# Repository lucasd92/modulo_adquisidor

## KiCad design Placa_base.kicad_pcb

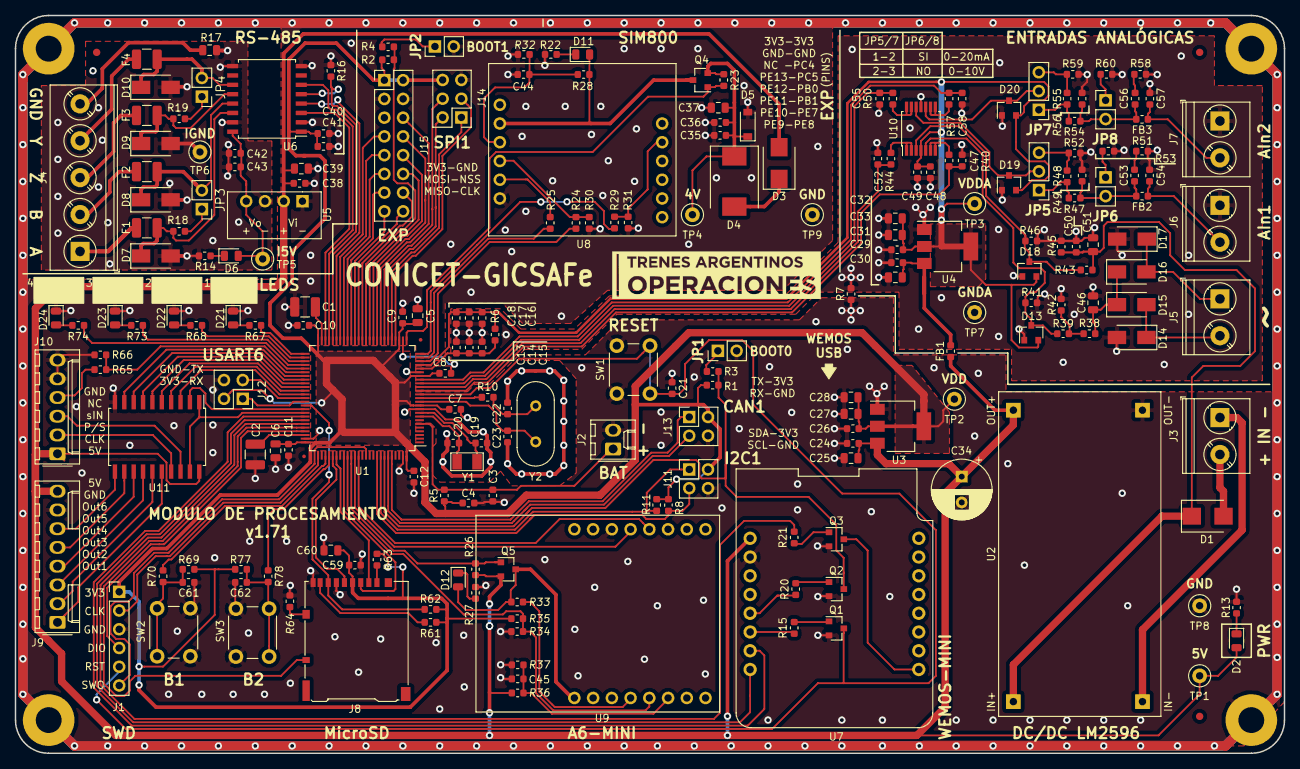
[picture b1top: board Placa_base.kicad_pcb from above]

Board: 2 copper layers, 172.0 x 100.0 mm, 228 parts (0 on the bottom side), 162 nets.

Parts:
C1, C2: 2.2uF; C_1210_3225Metric
C3, C15, C17, C40, C42, C48: 1Uf; C_0603_1608Metric
C4, C7, C8, C9, C10, C11, C12, C14, C16, C21, C24, C26, C29, C31, C38, C41, C43, C44, C45, C47, C49, C50, C52, C55, C58, C59, C61, C62: 100nF; C_0603_1608Metric
C5, C6: 4.7uF; C_0805_2012Metric
C13, C18: 10nF; C_0603_1608Metric
C19, C20: 1.5pF; C_0603_1608Metric
C22, C23: 20pF; C_0603_1608Metric
C25, C27, C28, C30, C32, C33, C37, C39, C46, C51, C60: 10uF; C_0805_2012Metric
C34: 820uF 10V; CP_Radial_D8.0mm_P3.50mm
C35: 10p; C_0603_1608Metric
C36: 33p; C_0603_1608Metric
C53, C56: 470pF; C_0603_1608Metric
C54, C57: 1nF; C_0603_1608Metric
D1, D3: S5JB-R5G; D_SMB
D2, D6, D11, D12, D21, D22, D23, D24: LED; LED_0805_2012Metric
D4: B340; D_SMC
D5: BZT52-B5V1X; D_SOD-123
D7, D8, D9, D10: SMAJ12CA-TR; D_SMA
D13, D18, D19, D20: BAV99; SOT-23
D14, D15, D16, D17: MRA4007T3G; D_SMA
F1, F2, F3, F4: USMF020; R_1210_3225Metric
FB1: Ferrite_Bead; R_0603_1608Metric
FB2, FB3: MMZ1608B601C; R_0603_1608Metric
FD1, FD2, FD3: Fiducial; Fiducial_1mm_Dia_2mm_Outer
FD4, FD5: Fiducial; Fiducial_0.5mm_Dia_1mm_Outer
G1: TrenesArgentinosLogo; TrenesArgentinosLogoNeg
H1, H2, H3, H4: MountingHole_Pad; MountingHole_3.5mm_Pad
J1: SWD/STLINK; PinHeader_1x06_P2.54mm_Vertical
J2: Bateria; Molex_KK-254_AE-6410-02A_1x02_P2.54mm_Vertical
J3: Entrada 24V; TerminalBlock_Phoenix_PT-1,5-2-5.0-H_1x02_P5.00mm_Horizonta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
J4: RS-485; TerminalBlock_Phoenix_PT-1,5-5-5.0-H_1x05_P5.00mm_Horizonta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
J5: TV_6V; TerminalBlock_Phoenix_PT-1,5-2-5.0-H_1x02_P5.00mm_Horizonta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
J6: AN1; TerminalBlock_Phoenix_PT-1,5-2-5.0-H_1x02_P5.00mm_Horizonta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
J7: AN2; TerminalBlock_Phoenix_PT-1,5-2-5.0-H_1x02_P5.00mm_Horizonta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
J8: Micro_SD_Card_Det_Hirose_DM3AT; microSD_HC_Hirose_DM3AT-SF-PEJM5
J9: Salidas 5V; Molex_KK-254_AE-6410-08A_1x08_P2.54mm_Vertical
J10: Interfaz con entradas digitales (CD4021); Molex_KK-254_AE-6410-06A_1x06_P2.54mm_Vertical
J11: I2C1; PinHeader_2x02_P2.54mm_Vertical
J12: USART6; PinHeader_2x02_P2.54mm_Vertical
J13: CAN1; PinHeader_2x02_P2.54mm_Vertical
J14: SPI1; PinHeader_2x03_P2.54mm_Vertical
J15: EXP; PinHeader_2x08_P2.54mm_Vertical
JP1, JP2: Jumper_2_Open; PinHeader_1x02_P2.54mm_Vertical
JP3, JP4: Jumper; PinHeader_1x02_P2.54mm_Vertical
JP5, JP7: 1/3-2/3; PinHeader_1x03_P2.54mm_Vertical
JP6, JP8: I_meas; PinHeader_1x02_P2.54mm_Vertical
Q1, Q2, Q3: MMBT3904; SOT-23
Q4, Q5: AO3401; SOT-23
R1, R2: 10K; R_0603_1608Metric
R3, R4: 510; R_0603_1608Metric
R5, R7, R28, R32, R33, R34, R35, R36, R37, R42, R45, R49, R56, R64: 0; R_0603_1608Metric
R6: 47; R_0603_1608Metric
R8, R11: 4K7; R_0603_1608Metric
R10: CALCULAR; R_0603_1608Metric
R13, R14, R22, R27, R70, R78: 1k; R_0603_1608Metric
R15, R20, R21, R24, R25, R29: 1K; R_0603_1608Metric
R16, R30, R31: 5K6; R_0603_1608Metric
R17: 100 1/2W; R_0805_2012Metric
R18, R19: 120; R_0603_1608Metric
R23, R26: 150k; R_0603_1608Metric
R38, R39, R41, R47, R48, R52, R54, R55, R59: 15k; R_0603_1608Metric
R40, R44, R50, R57: 1.5k; R_0603_1608Metric
R43: 47k; R_0603_1608Metric
R46: 12k; R_0603_1608Metric
R51, R58: 4.7; R_0603_1608Metric
R53, R60, R65: 220; R_0603_1608Metric
R61, R62, R63: 56K; R_0603_1608Metric
R66: 330; R_0603_1608Metric
R67, R68, R73, R74: 260; R_0603_1608Metric
R69, R77: 10k; R_0603_1608Metric
SW1, SW2, SW3: SW_Push; SW_PUSH_6mm_H9.5mm
TP1, TP2, TP3, TP4, TP5, TP6, TP7, TP8, TP9: TestPoint; TestPoint_Loop_D2.50mm_Drill1.0mm
U1: STM32F407VGTx; LQFP-100
U2: DC-DC_Step-Down; modulo_dc-dc-LM2596
U3, U4: AZ1117-3.3; SOT-223-3_TabPin2
U5: RFM-0505S; SIP4-RFM0505S
U6: ISO1412; SOIC-16W_7.5x10.3mm_P1.27mm
U7: WeMos_mini; wemos-d1-mini-with-pin-header-and-connector
U8: SIM800L_modulo; SIM800L_mod
U9: Modulo_A6_Mini; Modulo_A6_mini
U10: MCP6L04T-E/ST; TSSOP-14_4.4x5mm_P0.65mm
U11: 74HCT541; SOIC-20W_7.5x12.8mm_P1.27mm
Y1: 32.768KHz; Cristal 32KHz
Y2: 8MHz; Crystal_HC49-4H_Vertical

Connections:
+4V: C35.1, C36.1, C37.1, D4.1, D5.1, Q4.2, R23.2, TP4.1
+5P: C42.1, C43.1, D6.2, TP5.1, U5.4, U6.16
+5V: C24.1, C25.1, C34.1, C38.1, C39.1, D2.2, D3.2, FB1.1, J9.8, J10.1, Q5.2, R26.1, R36.2, TP1.1, U2.3, U3.3, U5.2, U7.1, U11.20
/A6_INT: R34.1, R35.2, U1.84, U9.5
/A6_ON: Q5.1, R26.2, U1.85
/An_In1: C47.1, R40.2, U1.15
/An_In2: C52.1, R44.2, U1.16
/An_In3: C55.1, R50.2, U1.17
/An_In4: C58.1, R57.2, U1.18
/BOOT0: Q2.3, R1.2, R3.1, U1.94
/CAN1_RX: J13.3, U1.95
/CAN1_TX: J13.1, U1.96
/DIO/in_clk: J10.2, U11.17
/DIO/par_ser: J10.3, U11.18
/EXP_PIN1: J15.6, U1.33
/EXP_PIN2: J15.7, U1.44
/EXP_PIN3: J15.8, U1.34
/EXP_PIN4: J15.9, U1.43
/EXP_PIN5: J15.10, U1.35
/EXP_PIN6: J15.11, U1.42
/EXP_PIN7: J15.12, U1.36
/EXP_PIN8: J15.13, U1.41
/EXP_PIN9: J15.14, U1.38
/EXP_PIN10: J15.15, U1.40
/EXP_PIN11: J15.16, U1.39
/I2C1_SCL: J11.3, R8.1, U1.92
/I2C1_SDA: J11.1, R11.1, U1.93
/IN_CLK: U1.62, U11.3
/IN_P-S: U1.66, U11.2
/IN_Read: R65.1, R66.2, U1.55
/LED1: R67.1, U1.51
/LED2: R68.1, U1.52
/LED3: R73.1, U1.53
/LED4: R74.1, U1.54
/MCU/PB2-BOOT1: R2.2, R4.1, U1.37
/MCU/PC14: C20.1, U1.8, Y1.2
/MCU/PC15: C19.1, U1.9, Y1.1
/MCU/PH0: C23.1, U1.12, Y2.2
/MCU/PH1: R10.1, U1.13
/MCU/TCK-SWCLK: J1.2, U1.76
/MCU/TDO-SWO: J1.6, U1.89
/MCU/TMS-SWDIO: J1.4, U1.72
/MCU/VBAT: C3.1, J2.1, R5.2, U1.6
/MCU/VREF+: C13.1, C14.1, C15.1, R6.2, U1.21
/NRST: C21.1, J1.5, Q1.3, SW1.1, U1.14
/OUT_1: U1.61, U11.4
/OUT_2: U1.60, U11.5
/OUT_3: U1.59, U11.6
/OUT_4: U1.58, U11.7
/OUT_5: U1.57, U11.8
/OUT_6: U1.56, U11.9
/OUT_EN: U1.67, U11.1, U11.19
/RS-485_D: U1.47, U6.6
/RS-485_DE: R16.2, U1.46, U6.5
/RS-485_R: U1.48, U6.3
/RS-485_RE: U1.45, U6.4
/Reset_ESP: R21.1, U1.70
/S800_DTR: R29.1, U1.25
/S800_ON: Q4.1, R23.1, U1.26
/SPI1_CK: J14.1, U1.30
/SPI1_MISO: J14.2, U1.31
/SPI1_MOSI: J14.4, U1.32
/SPI1_NSS: J14.3, U1.29
/SW1: R70.2, U1.78
/SW2: R78.2, U1.79
/USART1_RX: U1.69, U7.8
/USART1_TX: U1.68, U7.7
/USART2_RX: U1.87, U9.12
/USART2_TX: U1.86, U9.13
/USART4_RX: R25.1, U1.24
/USART4_TX: R24.1, U1.23
/USART6_RX: J12.1, U1.64
/USART6_TX: J12.3, U1.63
/WiFi/A: D7.1, F1.2, R18.2, U6.14
/WiFi/B: D8.1, F2.2, JP3.2, U6.13
/WiFi/DTR_SIM800: R29.2, R31.2, U8.11
/WiFi/RX_SIM800: R24.2, R30.2, U8.4
/WiFi/TX_SIM800: R25.2, U8.5
/WiFi/Y: D10.1, F4.2, JP4.2, U6.11
/WiFi/Z: D9.1, F3.2, R19.2, U6.12
/analogico/AIn1: C50.1, C51.1, D1.1, R43.1, R45.1, U2.1
/uSD_CD: J8.2, U1.81
/uSD_CK: J8.5, U1.80
/uSD_Cmd: J8.3, U1.83
/uSD_D0: J8.7, R62.1, U1.65
/uSD_Det: J8.10, U1.71
Earth: C42.2, C43.2, D7.2, D8.2, D9.2, D10.2, R14.1, R17.1, TP6.1, U5.3, U6.9, U6.15
GND: C1.2, C2.2, C3.2, C4.2, C5.2, C6.2, C7.2, C8.2, C9.2, C10.2, C11.2, C12.2, C19.2, C20.2, C21.2, C22.2, C23.2, C24.2, C25.2, C26.2, C27.2, C28.2, C34.2, C35.2, C36.2, C37.2, C38.2, C39.2, C40.2, C41.2, C44.2, C45.2, C59.2, C60.2, C61.2, C62.2, D5.2, D21.1, D22.1, D23.1, D24.1, H1.1, H2.1, H3.1, H4.1, J1.3, J2.2, J8.6, J8.9, J9.7, J10.5, J10.6, J11.4, J12.4, J13.4, J14.5, J15.3, J15.4, JP1.2, JP2.2, Q1.2, Q2.2, Q3.2, R7.1, R13.2, R16.1, R22.1, R27.1, R30.1, R31.1, R32.1, R35.1, R37.1, R64.1, R66.1, SW1.2, SW2.2, SW3.2, TP8.1, TP9.1, U1.10, U1.27, U1.74, U1.99, U2.4, U3.1, U5.1, U6.2, U6.8, U7.2, U8.6, U9.14, U11.10
GNDA: C13.2, C14.2, C15.2, C16.2, C17.2, C18.2, C29.2, C30.2, C31.2, C32.2, C33.2, C46.2, C47.2, C48.2, C49.2, C50.2, C51.2, C52.2, C54.2, C55.2, C57.2, C58.2, D13.1, D14.2, D16.2, D18.1, D19.1, D20.1, J6.1, J7.1, R7.2, R41.2, R42.2, R45.2, R46.2, R49.2, R51.1, R52.2, R53.1, R56.2, R58.1, R59.2, R60.1, TP7.1, U1.20, U4.1, U10.11
unnamed: C1.1, U1.49
unnamed: C2.1, U1.73
unnamed: C22.1, R10.2, Y2.1
unnamed: C29.1, C30.1, FB1.2, U4.3
unnamed: C44.1, R28.1, R32.2, U8.3
unnamed: C45.1, R36.1, R37.2, U9.6
unnamed: C46.1, D15.1, D17.1, R38.2
unnamed: C53.1, FB2.2, JP6.2, R47.2, R49.1
unnamed: C53.2, R51.2
unnamed: C54.1, FB2.1, J6.2
unnamed: C56.1, FB3.2, JP8.2, R54.2, R56.1
unnamed: C56.2, R58.2
unnamed: C57.1, FB3.1, J7.2
unnamed: C61.1, R69.1, R70.1, SW2.1
unnamed: C62.1, R77.1, R78.1, SW3.1
unnamed: D1.2, J3.2
unnamed: D2.1, R13.1
unnamed: D3.1, D4.2
unnamed: D6.1, R14.2
unnamed: D11.1, R22.2
unnamed: D11.2, Q4.3, R28.2, U8.2
unnamed: D12.1, R27.2
unnamed: D12.2, Q5.3, R33.1, U9.1
unnamed: D13.3, R39.2, R41.1, U10.5
unnamed: D14.1, D15.2, J5.2
unnamed: D16.1, D17.2, J5.1
unnamed: D18.3, R43.2, R46.1, U10.3
unnamed: D19.3, JP5.2, U10.12
unnamed: D20.3, JP7.2, U10.10
unnamed: D21.2, R67.2
unnamed: D22.2, R68.2
unnamed: D23.2, R73.2
unnamed: D24.2, R74.2
unnamed: F1.1, J4.1
unnamed: F2.1, J4.2
unnamed: F3.1, J4.3
unnamed: F4.1, J4.4
unnamed: J3.1, U2.2
unnamed: J4.5, R17.2
unnamed: J8.1, R63.1
unnamed: J8.8, R61.1
unnamed: J8.11, R64.2
unnamed: J9.1, U11.16
unnamed: J9.2, U11.15
unnamed: J9.3, U11.14
unnamed: J9.4, U11.13
unnamed: J9.5, U11.12
unnamed: J9.6, U11.11
unnamed: J10.4, R65.2
unnamed: JP1.1, R3.2
unnamed: JP2.1, R4.2
unnamed: JP3.1, R18.1
unnamed: JP4.1, R19.1
unnamed: JP5.1, R47.1, R48.1
unnamed: JP5.3, R48.2, R52.1
unnamed: JP6.1, R53.2
unnamed: JP7.1, R54.1, R55.1
unnamed: JP7.3, R55.2, R59.1
unnamed: JP8.1, R60.2
unnamed: Q1.1, R15.1
unnamed: Q2.1, R20.1
unnamed: Q3.1, R21.2
unnamed: Q3.3, U7.9
unnamed: R15.2, U7.6
unnamed: R20.2, U7.5
unnamed: R33.2, U9.4
unnamed: R38.1, R39.1, R42.1
unnamed: R40.1, U10.6, U10.7
unnamed: R44.1, U10.1, U10.2
unnamed: R50.1, U10.13, U10.14
unnamed: R57.1, U10.8, U10.9
VDD: C4.1, C5.1, C6.1, C7.1, C8.1, C9.1, C10.1, C11.1, C12.1, C26.1, C27.1, C28.1, C40.1, C41.1, C59.1, C60.1, J1.1, J8.4, J11.2, J12.2, J13.2, J14.6, J15.1, J15.2, R1.1, R2.1, R5.1, R8.2, R11.2, R34.2, R61.2, R62.2, R63.2, R69.2, R77.2, TP2.1, U1.11, U1.19, U1.28, U1.50, U1.75, U1.100, U3.2, U6.1
VDDA: C16.1, C17.1, C18.1, C31.1, C32.1, C33.1, C48.1, C49.1, D13.2, D18.2, D19.2, D20.2, R6.1, TP3.1, U1.22, U4.2, U10.4

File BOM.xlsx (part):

Eeschema (5.0.2)-1
Component Count: | 212
Ref | Qty | Value | Part | Footprint | Column1 | Datasheet | Description | Vendor
C1, C2 | 2 | 2.2uF | C | Capacitor_SMD:C_1210_3225Metric | 478-2402-1-ND | https://www.digikey.com/product-detail/en/avx-corporation/TP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 | Unpolarized capacitor
C3, C15, C17, C40, C42, C48 | 6 | 1Uf | C | Capacitor_SMD:C_0603_1608Metric | 1276-1019-1-ND | https://www.digikey.com/product-detail/en/samsung-electro-me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 | Unpolarized capacitor
C4, C7, C8, C9, C10, C11, C12, C14, C16, C21, C24, C26, C29, C31, C38, C41, C43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 | 28 | 100nF | C | Capacitor_SMD:C_0603_1608Metric | 1276-1000-1-ND | https://www.digikey.com/product-detail/en/samsung-electro-me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 | Unpolarized capacitor
C5, C6 | 2 | 4.7uF | C | Capacitor_SMD:C_0805_2012Metric | 445-14527-1-ND | https://www.digikey.com/product-detail/en/tdk-corporation/C2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 | Unpolarized capacitor
C13, C18 | 2 | 10nF | C | Capacitor_SMD:C_0603_1608Metric | 1276-1009-1-ND | https://www.digikey.com/product-detail/en/samsung-electro-me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 | Unpolarized capacitor
C19, C20 | 2 | 1.5pF | C | Capacitor_SMD:C_0603_1608Metric | 311-1737-1-ND | https://www.digikey.com/product-detail/es/yageo/CC0603BRNPO9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 | Unpolarized capacitor
C22, C23 | 2 | 20pF | C | Capacitor_SMD:C_0603_1608Metric | 311-3924-1-ND | https://www.digikey.com/product-detail/en/yageo/CC0603GRNPO9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 | Unpolarized capacitor
C25, C27, C28, C30, C32, C33, C37, C39, C46, C51, C60 | 11 | 10uF | C | Capacitor_SMD:C_0805_2012Metric | 490-10498-1-ND | https://www.digikey.com/product-detail/en/murata-electronics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 | Unpolarized capacitor
C34 | 1 | 820uF 10V | CP | Capacitor_THT:CP_Radial_D8.0mm_P3.50mm | 399-14115-ND | https://www.digikey.com/product-detail/en/kemet/A755KS827M1A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 | Polarized capacitor
C35 | 1 | 10p | C | Capacitor_SMD:C_0603_1608Metric | 732-7760-1-ND | https://www.digikey.com/product-detail/en/wurth-electronics-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 | Unpolarized capacitor
C36 | 1 | 33p | C | Capacitor_SMD:C_0603_1608Metric | 478-10278-1-ND | https://www.digikey.com/product-detail/en/avx-corporation/06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 | Unpolarized capacitor
C53, C56 | 2 | 470pF | C | Capacitor_SMD:C_0603_1608Metric | 1276-1094-1-ND | https://www.digikey.com/product-detail/en/samsung-electro-me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 | Unpolarized capacitor
C54, C57 | 2 | 1nF | C | Capacitor_SMD:C_0603_1608Metric | 1276-1018-1-ND | https://www.digikey.com/product-detail/en/samsung-electro-me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 | Unpolarized capacitor
D1, D3 | 2 | S5JB-R5G | 1N4007 | Diode_SMD:D_SMB | S5JBR5GCT-ND | https://www.digikey.com/product-detail/en/taiwan-semiconduct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 | 1000V 1A General Purpose Rectifier Diode, DO-41
D2, D6, D11, D12, D21, D22, D23, D24 | 8 | LED | LED | LED_SMD:LED_0805_2012Metric |  | ~ | Light emitting diode
D4 | 1 | B340 | B340 | Diode_SMD:D_SMC | B340-FDICT-ND | https://www.digikey.com/product-detail/en/diodes-incorporate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 | 40V 3A Schottky Barrier Rectifier Diode, SMC
D5 | 1 | BZT52-B5V1X | ZPDxx | Diode_SMD:D_SOD-123 | 1727-7681-1-ND | https://www.digikey.com/product-detail/en/nexperia-usa-inc/B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 | 500mW Zener Diode, DO-35
D7, D8, D9, D10 | 4 | SMAJ12CA-TR | D_TVS | Diode_SMD:D_SMA | 497-2996-1-ND | https://www.digikey.com/product-detail/en/stmicroelectronics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 | Bidirectional transient-voltage-suppression diode
D13, D18, D19, D20 | 4 | BAV99 | BAV99 | Package_TO_SOT_SMD:SOT-23 | BAV99LT1GOSCT-ND | https://www.digikey.com/product-detail/en/on-semiconductor/B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 | BAV99 High-speed switching diodes
D14, D15, D16, D17 | 4 | MRA4007T3G | MRA4007T3G | Diode_SMD:D_SMA | 641-1018-1-ND | https://www.digikey.com/product-detail/en/comchip-technology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 | 1000V 1A General Purpose Rectifier Diode, SMA(DO-214AC)
F1, F2, F3, F4 | 4 | USMF020 | Fuse | Resistor_SMD:R_1210_3225Metric | MF-USMF020-2CT-ND | https://www.digikey.com/product-detail/es/bourns-inc/MF-USMF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 | Fuse
FB1 | 1 | Ferrite_Bead | Ferrite_Bead | Resistor_SMD:R_0603_1608Metric | 445-2205-1-ND | https://www.digikey.com/product-detail/en/tdk-corporation/MP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 | Ferrite bead
FB2, FB3 | 2 | MMZ1608B601C | Ferrite_Bead_Small | Resistor_SMD:R_0603_1608Metric | 445-2166-1-ND | https://www.digikey.com/product-detail/en/tdk-corporation/MM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 | Ferrite bead, small symbol
J1 | 1 | SWD/STLINK | Conn_01x06_Male | Connector_PinHeader_2.54mm:PinHeader_1x06_P2.54mm_Vertical |  | ~
J2 | 1 | Bateria | Conn_01x02_Male | Connector_Molex:Molex_KK-254_AE-6410-02A_1x02_P2.54mm_Vertical |  | ~
J3 | 1 | Entrada 24V | Screw_Terminal_01x02 | Propios:TerminalBlock_Phoenix_PT-1,5-2-5.0-H_1x02_P5.00mm_Horizontal_con_modelo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 |  | ~
J4 | 1 | RS-485 | Screw_Terminal_01x05 | Propios:TerminalBlock_Phoenix_PT-1,5-5-5.0-H_1x05_P5.00mm_Horizontal_con_modelo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 |  | ~
J5 | 1 | TV_6V | Screw_Terminal_01x02 | Propios:TerminalBlock_Phoenix_PT-1,5-2-5.0-H_1x02_P5.00mm_Horizontal_con_modelo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 |  | ~
J6 | 1 | AN1 | Screw_Terminal_01x02 | Propios:TerminalBlock_Phoenix_PT-1,5-2-5.0-H_1x02_P5.00mm_Horizontal_con_modelo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 |  | ~
J7 | 1 | AN2 | Screw_Terminal_01x02 | Propios:TerminalBlock_Phoenix_PT-1,5-2-5.0-H_1x02_P5.00mm_Horizontal_con_modelo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 |  | ~
J8 | 1 | Micro_SD | Micro_SD_Card_Det_Hirose_DM3AT | Propios:microSD_HC_Hirose_DM3AT-SF-PEJM5 | HR1964CT-ND | https://www.digikey.com/product-detail/es/hirose-electric-co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
J9 | 1 | Salidas 5V | Conn_01x08_Male | Connector_Molex:Molex_KK-254_AE-6410-08A_1x08_P2.54mm_Vertical |  | ~
J10 | 1 | entradas digitales | Conn_01x06_Male | Connector_Molex:Molex_KK-254_AE-6410-06A_1x06_P2.54mm_Vertical |  | ~
J11 | 1 | I2C1 | Conn_02x02_Odd_Even | Connector_PinHeader_2.54mm:PinHeader_2x02_P2.54mm_Vertical |  | ~
J12 | 1 | USART6 | Conn_02x02_Odd_Even | Connector_PinHeader_2.54mm:PinHeader_2x02_P2.54mm_Vertical |  | ~
J13 | 1 | CAN1 | Conn_02x02_Odd_Even | Connector_PinHeader_2.54mm:PinHeader_2x02_P2.54mm_Vertical |  | ~
J14 | 1 | SPI1 | Conn_02x03_Odd_Even | Connector_PinHeader_2.54mm:PinHeader_2x03_P2.54mm_Vertical |  | ~
J15 | 1 | Conn_02x08_Odd_Even | Conn_02x08_Odd_Even | Connector_PinHeader_2.54mm:PinHeader_2x08_P2.54mm_Vertical |  | ~
JP1, JP2 | 2 | Jumper_2_Open | Jumper_2_Open | Connector_PinHeader_2.54mm:PinHeader_1x02_P2.54mm_Vertical |  | ~ | Jumper, 2-pole, open
JP3, JP4 | 2 | Jumper | Jumper | Connector_PinHeader_2.54mm:PinHeader_1x02_P2.54mm_Vertical |  | ~ | Jumper, normally closed
JP5, JP7 | 2 | 1/3-2/3 | Jumper_3_Open | Connector_PinHeader_2.54mm:PinHeader_1x03_P2.54mm_Vertical |  | ~ | Jumper, 3-pole, both open
JP6, JP8 | 2 | I_meas | Jumper | Connector_PinHeader_2.54mm:PinHeader_1x02_P2.54mm_Vertical |  | ~ | Jumper, normally closed
Q1, Q2, Q3 | 3 | MMBT3904 | MMBT3904 | Package_TO_SOT_SMD:SOT-23 | MMBT3904TPMSCT-ND | https://www.digikey.com/product-detail/en/micro-commercial-c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 | 0.2A Ic, 40V Vce, Small Signal NPN Transistor, SOT-23
Q4, Q5 | 2 | AO3401 | BSS83P | Package_TO_SOT_SMD:SOT-23 | 785-1001-1-ND | https://www.digikey.com/product-detail/en/alpha-omega-semico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 | -0.33A Id, -60V Vds, P-Channel MOSFET, SOT-23-3
R1, R2,R69, R77 | 4 | 10K | R | Resistor_SMD:R_0603_1608Metric | RMCF0603FT10K0CT-ND | https://www.digikey.com/product-detail/en/stackpole-electron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 | Resistor
R3, R4 | 2 | 510 | R | Resistor_SMD:R_0603_1608Metric | RMCF0603FT510RCT-ND | https://www.digikey.com/product-detail/en/stackpole-electron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 | Resistor
R5, R7, R9, R12, R28, R32, R33, R34, R35, R36, R37, R42, R45, R49, R56, R64 | 17 | 0 | R | Resistor_SMD:R_0603_1608Metric | RMCF0603ZT0R00CT-ND | https://www.digikey.com/product-detail/en/stackpole-electron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 | Resistor
R6 | 1 | 47 | R | Resistor_SMD:R_0603_1608Metric | RMCF0603FT47R0CT-ND | https://www.digikey.com/product-detail/en/stackpole-electron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 | Resistor
R8, R11 | 2 | 4K7 | R | Resistor_SMD:R_0603_1608Metric | RMCF0603FT4K70CT-ND | https://www.digikey.com/product-detail/en/stackpole-electron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 | Resistor
R10 | 0 | CALCULAR | R | Resistor_SMD:R_0603_1608Metric |  | ~ | Resistor
R15, R20, R21, R24, R25, R29,R13, R14, R22,R27,R70, R78 | 12 | 1K | R | Resistor_SMD:R_0603_1608Metric | RMCF0603FT1K00CT-ND | https://www.digikey.com/product-detail/en/stackpole-electron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 | Resistor
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
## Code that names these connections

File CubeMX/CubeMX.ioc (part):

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Mcu.Name=STM32F407V(E-G)Tx
Mcu.Package=LQFP100
Mcu.UserName=STM32F407VGTx
PA0-WKUP.GPIOParameters=GPIO_Label
PA0-WKUP.GPIO_Label=S800_UART4_TX
PA0-WKUP.Mode=Asynchronous
PA0-WKUP.Signal=UART4_TX
PA1.GPIOParameters=GPIO_Label
PA1.GPIO_Label=S800_UART4_RX
PA1.Mode=Asynchronous
PA1.Signal=UART4_RX
PA10.GPIOParameters=GPIO_Label
PA10.GPIO_Label=WIFI_UART1_RX
PA10.Mode=Asynchronous
PA10.Signal=USART1_RX
PA11.GPIOParameters=GPIO_Label
PA11.GPIO_Label=WIFI_RESET
PA11.Signal=GPIO_Output
PA12.GPIOParameters=GPIO_Label
PA12.GPIO_Label=SD_DETECT
PA12.Signal=GPIO_Input
PA13.GPIOParameters=GPIO_Label
PA13.GPIO_Label=SWD_DIO
PA13.Mode=Trace_Asynchronous_SW
PA13.Signal=SYS_JTMS-SWDIO
PA14.GPIOParameters=GPIO_Label
PA14.GPIO_Label=SWD_CLK
PA14.Mode=Trace_Asynchronous_SW
PA14.Signal=SYS_JTCK-SWCLK
PA15.GPIOParameters=GPIO_Label
PA15.GPIO_Label=__FLOATING__
PA15.Signal=GPIO_Analog
PA2.GPIOParameters=GPIO_Label
PA2.GPIO_Label=S800_UART4_DTR
PA2.Signal=GPIO_Output
PA3.GPIOParameters=GPIO_Label
PA3.GPIO_Label=S800_ON
PA3.Signal=GPIO_Output
PA4.Mode=NSS_Signal_Hard_Output
PA4.Signal=SPI1_NSS
PA5.Mode=Full_Duplex_Master
PA5.Signal=SPI1_SCK
PA6.Mode=Full_Duplex_Master
PA6.Signal=SPI1_MISO
PA7.Mode=Full_Duplex_Master
PA7.Signal=SPI1_MOSI
PA8.GPIOParameters=GPIO_Label
PA8.GPIO_Label=OUT_EN
PA8.Signal=GPIO_Output
PA9.GPIOParameters=GPIO_Label
PA9.GPIO_Label=WIFI_UART1_TX
PA9.Mode=Asynchronous
PA9.Signal=USART1_TX
PB0.GPIOParameters=GPIO_Label
PB0.GPIO_Label=EXP_PIN_5
PB0.Signal=GPIO_Output
PB1.GPIOParameters=GPIO_Label
PB1.GPIO_Label=EXP_PIN_7
PB1.Signal=GPIO_Output
PB10.GPIOParameters=GPIO_Label
PB10.GPIO_Label=RS485_D_TX
PB10.Mode=Asynchronous
PB10.Signal=USART3_TX
PB11.GPIOParameters=GPIO_Label
PB11.GPIO_Label=RS485_R_RX
PB11.Mode=Asynchronous
PB11.Signal=USART3_RX
PB12.GPIOParameters=GPIO_Label
PB12.GPIO_Label=LED_1
PB12.Signal=GPIO_Output
PB13.GPIOParameters=GPIO_Label
PB13.GPIO_Label=LED_2
PB13.Signal=GPIO_Output
PB14.GPIOParameters=GPIO_Label
PB14.GPIO_Label=LED_3
PB14.Signal=GPIO_Output
PB15.GPIOParameters=GPIO_Label
PB15.GPIO_Label=LED_4
PB15.Signal=GPIO_Output
PB2.GPIOParameters=GPIO_Label
PB2.GPIO_Label=BOOT1
PB2.Signal=GPIO_Input
PB3.GPIOParameters=GPIO_Label
PB3.GPIO_Label=SWD_SWO
PB3.Mode=Trace_Asynchronous_SW
PB3.Signal=SYS_JTDO-SWO
PB4.GPIOParameters=GPIO_Label
PB4.GPIO_Label=__FLOATING__
PB4.Signal=GPIO_Analog
PB5.GPIOParameters=GPIO_Label
PB5.GPIO_Label=__FLOATING__
PB5.Signal=GPIO_Analog
PB6.GPIOParameters=GPIO_PuPdOD
PB6.GPIO_PuPdOD=GPIO_NOPULL
PB6.Mode=I2C
PB6.Signal=I2C1_SCL
PB7.GPIOParameters=GPIO_PuPdOD
PB7.GPIO_PuPdOD=GPIO_NOPULL
PB7.Mode=I2C
PB7.Signal=I2C1_SDA
PB8.Mode=Master
PB8.Signal=CAN1_RX
PB9.Mode=Master
PB9.Signal=CAN1_TX
PC0.GPIOParameters=GPIO_Label
PC0.GPIO_Label=ADC1_IN10_An_In1
PC0.Signal=ADCx_IN10
PC1.GPIOParameters=GPIO_Label
PC1.GPIO_Label=ADC1_IN11_An_In2
PC1.Signal=ADCx_IN11
PC10.GPIOParameters=GPIO_Label
PC10.GPIO_Label=B1
PC10.Signal=GPIO_Input
PC11.GPIOParameters=GPIO_Label
PC11.GPIO_Label=B2
PC11.Signal=GPIO_Input
PC12.Mode=SD_1_bit
PC12.Signal=SDIO_CK
PC13-ANTI_TAMP.GPIOParameters=GPIO_Label
PC13-ANTI_TAMP.GPIO_Label=__FLOATING__
PC13-ANTI_TAMP.Signal=GPIO_Analog
PC14-OSC32_IN.Mode=LSE-External-Oscillator
PC14-OSC32_IN.Signal=RCC_OSC32_IN
PC15-OSC32_OUT.Mode=LSE-External-Oscillator
PC15-OSC32_OUT.Signal=RCC_OSC32_OUT
PC2.GPIOParameters=GPIO_Label
PC2.GPIO_Label=ADC1_IN12_An_In3
PC2.Signal=ADCx_IN12
PC3.GPIOParameters=GPIO_Label
PC3.GPIO_Label=ADC1_IN13_An_In4
PC3.Signal=ADCx_IN13
PC4.GPIOParameters=GPIO_Label
PC4.GPIO_Label=EXP_PIN_1
PC4.Signal=GPIO_Output
PC5.GPIOParameters=GPIO_Label
PC5.GPIO_Label=EXP_PIN_3
PC5.Signal=GPIO_Output
PC6.Mode=Asynchronous
PC6.Signal=USART6_TX
PC7.Mode=Asynchronous
PC7.Signal=USART6_RX
PC8.Mode=SD_1_bit
PC8.Signal=SDIO_D0
PC9.GPIOParameters=GPIO_Label
PC9.GPIO_Label=IN_PS
PC9.Signal=GPIO_Output
PD0.GPIOParameters=GPIO_Label
PD0.GPIO_Label=SD_CD
PD0.Signal=GPIO_Input
PD1.GPIOParameters=GPIO_Label
PD1.GPIO_Label=__FLOATING__
PD1.Signal=GPIO_Analog
PD10.GPIOParameters=GPIO_Label
PD10.GPIO_Label=OUT_5
PD10.Signal=GPIO_Output
PD11.GPIOParameters=GPIO_Label
PD11.GPIO_Label=OUT_4
PD11.Signal=GPIO_Output
PD12.GPIOParameters=GPIO_Label
PD12.GPIO_Label=OUT_3
PD12.Signal=GPIO_Output
PD13.GPIOParameters=GPIO_Label
PD13.GPIO_Label=OUT_2
PD13.Signal=GPIO_Output
PD14.GPIOParameters=GPIO_Label
PD14.GPIO_Label=OUT_1
PD14.Signal=GPIO_Output
PD15.GPIOParameters=GPIO_Label
PD15.GPIO_Label=IN_CLK
PD15.Signal=GPIO_Output
PD2.Mode=SD_1_bit
PD2.Signal=SDIO_CMD
PD3.GPIOParameters=GPIO_Label
PD3.GPIO_Label=A6_INT
PD3.Signal=GPIO_Output
PD4.GPIOParameters=GPIO_Label
PD4.GPIO_Label=A6_ON
PD4.Signal=GPIO_Output
PD5.GPIOParameters=GPIO_Label
PD5.GPIO_Label=A6_UART2_TX
PD5.Mode=Asynchronous
PD5.Signal=USART2_TX
PD6.GPIOParameters=GPIO_Label
PD6.GPIO_Label=A6_UART2_RX
PD6.Mode=Asynchronous
PD6.Signal=USART2_RX
PD7.GPIOParameters=GPIO_Label
PD7.GPIO_Label=__FLOATING__
PD7.Signal=GPIO_Analog
PD8.GPIOParameters=GPIO_Label
PD8.GPIO_Label=IN_READ
PD8.Signal=GPIO_Input
PD9.GPIOParameters=GPIO_Label
PD9.GPIO_Label=OUT_6
PD9.Signal=GPIO_Output
PE0.GPIOParameters=GPIO_Label
PE0.GPIO_Label=__FLOATING__
PE0.Signal=GPIO_Analog
PE1.GPIOParameters=GPIO_Label
PE1.GPIO_Label=__FLOATING__
PE1.Signal=GPIO_Analog
PE10.GPIOParameters=GPIO_Label
PE10.GPIO_Label=EXP_PIN_8
PE10.Signal=GPIO_Output
PE11.GPIOParameters=GPIO_Label
PE11.GPIO_Label=EXP_PIN_6
PE11.Signal=GPIO_Output
PE12.GPIOParameters=GPIO_Label
PE12.GPIO_Label=EXP_PIN_4
PE12.Signal=GPIO_Output
PE13.GPIOParameters=GPIO_Label
PE13.GPIO_Label=EXP_PIN_2
PE13.Signal=GPIO_Output
PE14.GPIOParameters=GPIO_Label
PE14.GPIO_Label=RS485_RE
PE14.Signal=GPIO_Output
PE15.GPIOParameters=GPIO_Label
PE15.GPIO_Label=RS485_DE
PE15.Signal=GPIO_Output
PE2.GPIOParameters=GPIO_Label
PE2.GPIO_Label=__FLOATING__
PE2.Signal=GPIO_Analog
PE3.GPIOParameters=GPIO_Label
PE3.GPIO_Label=__FLOATING__
PE3.Signal=GPIO_Analog
PE4.GPIOParameters=GPIO_Label
PE4.GPIO_Label=__FLOATING__
PE4.Signal=GPIO_Analog
PE5.GPIOParameters=GPIO_Label
PE5.GPIO_Label=__FLOATING__
PE5.Signal=GPIO_Analog
PE6.GPIOParameters=GPIO_Label
PE6.GPIO_Label=__FLOATING__
PE6.Signal=GPIO_Analog
PE7.GPIOParameters=GPIO_Label
PE7.GPIO_Label=EXP_PIN_9
PE7.Signal=GPIO_Output
PE8.GPIOParameters=GPIO_Label
PE8.GPIO_Label=EXP_PIN_11
PE8.Signal=GPIO_Output
PE9.GPIOParameters=GPIO_Label
PE9.GPIO_Label=EXP_PIN_10
PE9.Signal=GPIO_Output
PH0-OSC_IN.Mode=HSE-External-Oscillator
PH0-OSC_IN.Signal=RCC_OSC_IN
PH1-OSC_OUT.Mode=HSE-External-Oscillator
PH1-OSC_OUT.Signal=RCC_OSC_OUT
RCC.HSE_VALUE=8000000
RCC.SYSCLKFreq_VALUE=168000000
RCC.SYSCLKSource=RCC_SYSCLKSOURCE_PLLCLK
board=custom

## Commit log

2019-05-22 v0.11 Primera versión incompleta
2019-05-22 V0.11
    Resuelto problema bibliotecas
2019-05-27 Selección definitiva de componentes
    Falta interconexión y comunicaciones vacantes.
2019-05-28 v0.14 interconexion completa
    Se terminó de conectar el MCU a los módulos y headers de expansión.
2019-05-31 v0.15
    Primera versión de hardware.
2019-06-04 v0.16
    Correcciones en PCB.
2019-06-04 v0.17
    Cambios en PCB y nueva versión de PDF.
2019-06-10 Modificaciones en planos de masa
    Se cambiaron algunas pistas y se agregó plano superior junto a vías para mejorar la impedancia.
2019-07-04 v0.19 pasa ERC con 0 errores/warnings.
2019-07-05 v0.191
    Cambios de Santiago + dirección etiquetas + CubeMX
2019-07-05 Modificaciones en PCB
2019-07-09 Importantes mejoras en PCB
2019-07-10 PCB 1.3. Re-ruteo de 5v, VCC, desacople, etc.
2019-07-10 Se corrige ruteo de pads en U11
2019-07-11 Cambio de I2C3 por USART6
    Cambio mínimo para que quede disponible la UART6
2019-07-12 Modificaciones menores en esquemático y PCB
    Se reemplazó I2C3 por USART6 (debug), se agregaron pull-ups en I2C1, reducción de agujeros de vías a 0.5mm y actualización de labels en esquemático.
2019-07-15 Reemplazo de todos los footprints
    Se reemplazaron todos los footprints para hacer soldadura por horno y se acomodó nuevamente la serigrafía.
2019-07-16 Cambios para reducir PCB
    Cambio de nodemcu por wemos y ajuste de todas las pistas
2019-07-16 Continuo con la reducción
    conecté las pistas faltantes, resta reducir los márgenes y planos de masa.
2019-07-17 Cambio de nodemcu a wemos y reducción
    Se finalizó la reducción del PCB junto con el reemplazo del nodemcu por wemos d1 mini.
2019-07-31 PCB v1.5
2019-08-02 PCB v1.51
    Agregado de Test-point, fiduciales y modelos 3D.
2019-08-02 PCB v1.51
    Actualización de comentarios.
2019-08-02 PCB 1.6. Optimizacion de 4V. Correccion de overlap entre impresiones de componentes.
2019-08-04 PCB 1.61: nombre de la placa y version
2019-08-06 PCB 1.62: serigrafía pines J10
    Actualización de PDF y cambios mínimos.
2019-08-06 PCB v1.62: Cambio de nombre
    Cambio de nombre a Módulo de procesamiento y versión a v1.62.
2019-08-07 Agregado de BOM
2019-08-15 BOM actualizada
    Se adaptó la BOM a un formato que pueda leer digikey,
2019-08-30 PCB 1.7
2019-09-14 PCB 1.71
